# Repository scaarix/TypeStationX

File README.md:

# TypeStationX

AKA PS2-KB

# Update
PCB arrived now waiting for parts to arrive

# About
a single mcu RP2040 based keyboard that uses ps2 controller connectors

currently in development
when ordering pcbs make sure to upload and order both<a href="https://github.com/scaarix/ps2-keyboard-thing/blob/main/TypeStationX/gerbers/left.zip"> left</a> and <a href="https://github.com/scaarix/ps2-keyboard-thing/blob/main/TypeStationX/gerbers/left.zip">right</a> sides
# Findings:
I don't think there are any ps2 controller extension cables that have all 9 pins available. Because one of the pins aren't needed, they get rid of it to save a few cents. So making your own cable is nessisary.
If i make a rev2 (i probably won't) it would most likely have an IO expander on the other half using spi (6 pins on the connector) so that I can use the cable instead of having to create my own.

# TODO:
- [x] Create firmware
- [ ] Create build guide
- [ ] Buy pcb and assemble
- [ ] Add photos

# Parts
| Part name                         | Amount       |Link                                                                                                   |
| --------------------------------- | ------------ | ------------------------------------------------------------------------------------------            |
| KB2040                            | 1            | <a href="https://www.adafruit.com/product/5302">Adafruit</a>|
| 1N4148W Diode                     | 36           |<a href="https://www.adafruit.com/product/5099">AdaFruit</a> |
| 1N4148TR Diode (THT)              | 36           | <a href="https://www.aliexpress.com/item/32729204179.html">Aliexpress</a>|
| Female controller ports           | 2            |<a href="https://www.aliexpress.com/item/1005005547168036.html?spm=a2g0o.productlist.main.47.63aa6e50gPBv1v&algo_pvid=186e3400-9a3a-4116-adb0-feedf2eab064">Aliexpress</a>|
| Male Controller Port              | 2            |<a href="https://www.aliexpress.com/item/1005003234151343.html">Aliexpress</a>|
| Your choice of mx switches        | 36           |                                                                                                       |
| 6mmx3mm magnets                   | 10           |<a href="https://www.amazon.com/FINDMAG-Magnets-Magnetic-Whiteboard-Refrigerator/dp/B08M3YP56J">Amazon</a>|

WARNING: Your PS2 controller cable extension may only have 8 out of the 9 pins needed. You can dissasemble the connector piece and add another pin yourself. Depending on your case it may be better just to use two ps2 controllers to make your own cable!

# HUGE THANKS TO
Chewiedies for helping make the stunning case :)

Corvett for giving me the idea for using the ps2 connector to bridge the two halfs of the keyboard

The absolem server for putting up with my sometimes stupid questions and helping me along the way

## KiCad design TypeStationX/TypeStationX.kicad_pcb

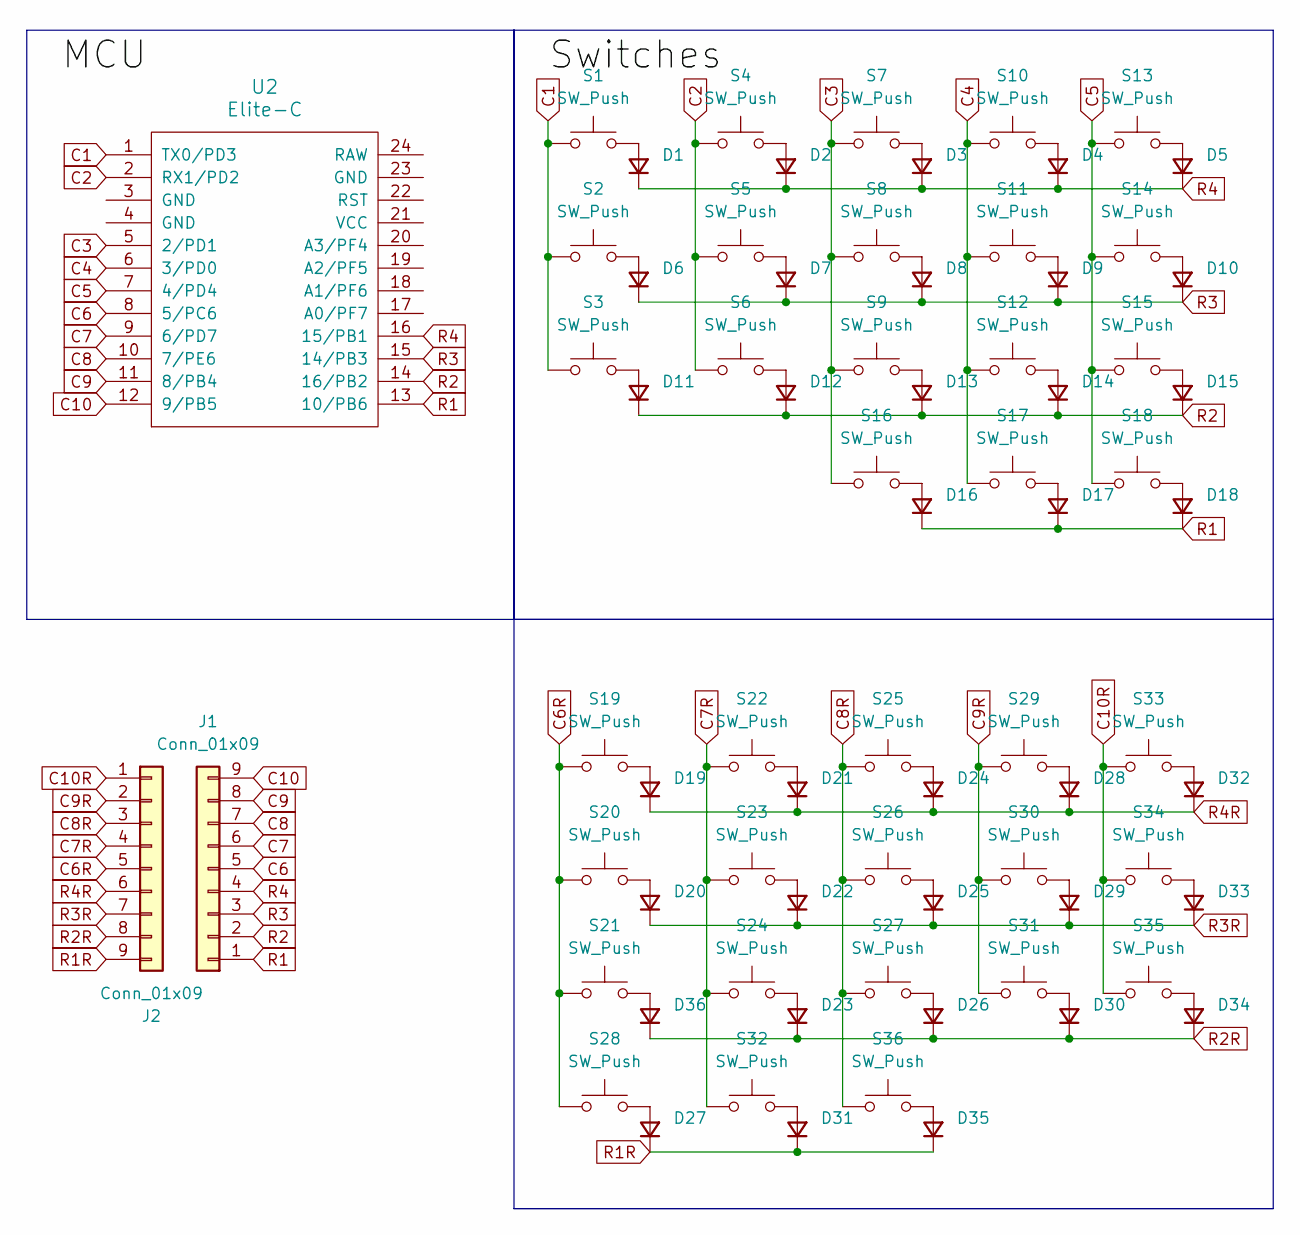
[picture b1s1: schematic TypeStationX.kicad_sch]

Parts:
D1, D2, D3, D4, D5, D6, D7, D8, D9, D10, D11, D12, D13, D14, D15, D16, D17, D18, D19, D20, D21, D22, D23, D24, D25, D26, D27, D28, D29, D30, D31, D32, D33, D34, D35, D36: D_Small; D3_TH_SMD_v2
J1, J2: Conn_01x09; 1x9 4mm
S1, S2, S3, S4, S5, S6, S7, S8, S9, S10, S11, S12, S13, S14, S15, S16, S17, S18, S19, S20, S21, S22, S23, S24, S25, S26, S27, S28, S29, S30, S31, S32, S33, S34, S35, S36: SW_Push; SW_Cherry_MX_PCB_1.00u
U2: Elite-C; ArduinoProMicro

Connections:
C1: S1.1, S2.1, S3.1, U2.1 (TX0/PD3)
C2: S4.1, S5.1, S6.1, U2.2 (RX1/PD2)
C3: S7.1, S8.1, S9.1, S16.1, U2.5 (2/PD1)
C4: S10.1, S11.1, S12.1, S17.1, U2.6 (3/PD0)
C5: S13.1, S14.1, S15.1, S18.1, U2.7 (4/PD4)
C6: J1.5, U2.8 (5/PC6)
C6R: J2.5, S19.1, S20.1, S21.1, S28.1
C7: J1.6, U2.9 (6/PD7)
C7R: J2.4, S22.1, S23.1, S24.1, S32.1
C8: J1.7, U2.10 (7/PE6)
C8R: J2.3, S25.1, S26.1, S27.1, S36.1
C9: J1.8, U2.11 (8/PB4)
C9R: J2.2, S29.1, S30.1, S31.1
C10: J1.9, U2.12 (9/PB5)
C10R: J2.1, S33.1, S34.1, S35.1
unnamed: D1.2 (A), S1.2
unnamed: D2.2 (A), S4.2
unnamed: D3.2 (A), S7.2
unnamed: D4.2 (A), S10.2
unnamed: D5.2 (A), S13.2
unnamed: D6.2 (A), S2.2
unnamed: D7.2 (A), S5.2
unnamed: D8.2 (A), S8.2
unnamed: D9.2 (A), S11.2
unnamed: D10.2 (A), S14.2
unnamed: D11.2 (A), S3.2
unnamed: D12.2 (A), S6.2
unnamed: D13.2 (A), S9.2
unnamed: D14.2 (A), S12.2
unnamed: D15.2 (A), S15.2
unnamed: D16.2 (A), S16.2
unnamed: D17.2 (A), S17.2
unnamed: D18.2 (A), S18.2
unnamed: D19.2 (A), S19.2
unnamed: D20.2 (A), S20.2
unnamed: D21.2 (A), S22.2
unnamed: D22.2 (A), S23.2
unnamed: D23.2 (A), S24.2
unnamed: D24.2 (A), S25.2
unnamed: D25.2 (A), S26.2
unnamed: D26.2 (A), S27.2
unnamed: D27.2 (A), S28.2
unnamed: D28.2 (A), S29.2
unnamed: D29.2 (A), S30.2
unnamed: D30.2 (A), S31.2
unnamed: D31.2 (A), S32.2
unnamed: D32.2 (A), S33.2
unnamed: D33.2 (A), S34.2
unnamed: D34.2 (A), S35.2
unnamed: D35.2 (A), S36.2
unnamed: D36.2 (A), S21.2
R1: D16.1 (K), D17.1 (K), D18.1 (K), J1.1, U2.13 (10/PB6)
R1R: D27.1 (K), D31.1 (K), D35.1 (K), J2.9
R2: D11.1 (K), D12.1 (K), D13.1 (K), D14.1 (K), D15.1 (K), J1.2, U2.14 (16/PB2)
R2R: D23.1 (K), D26.1 (K), D30.1 (K), D34.1 (K), D36.1 (K), J2.8
R3: D6.1 (K), D7.1 (K), D8.1 (K), D9.1 (K), D10.1 (K), J1.3, U2.15 (14/PB3)
R3R: D20.1 (K), D22.1 (K), D25.1 (K), D29.1 (K), D33.1 (K), J2.7
R4: D1.1 (K), D2.1 (K), D3.1 (K), D4.1 (K), D5.1 (K), J1.4, U2.16 (15/PB1)
R4R: D19.1 (K), D21.1 (K), D24.1 (K), D28.1 (K), D32.1 (K), J2.6

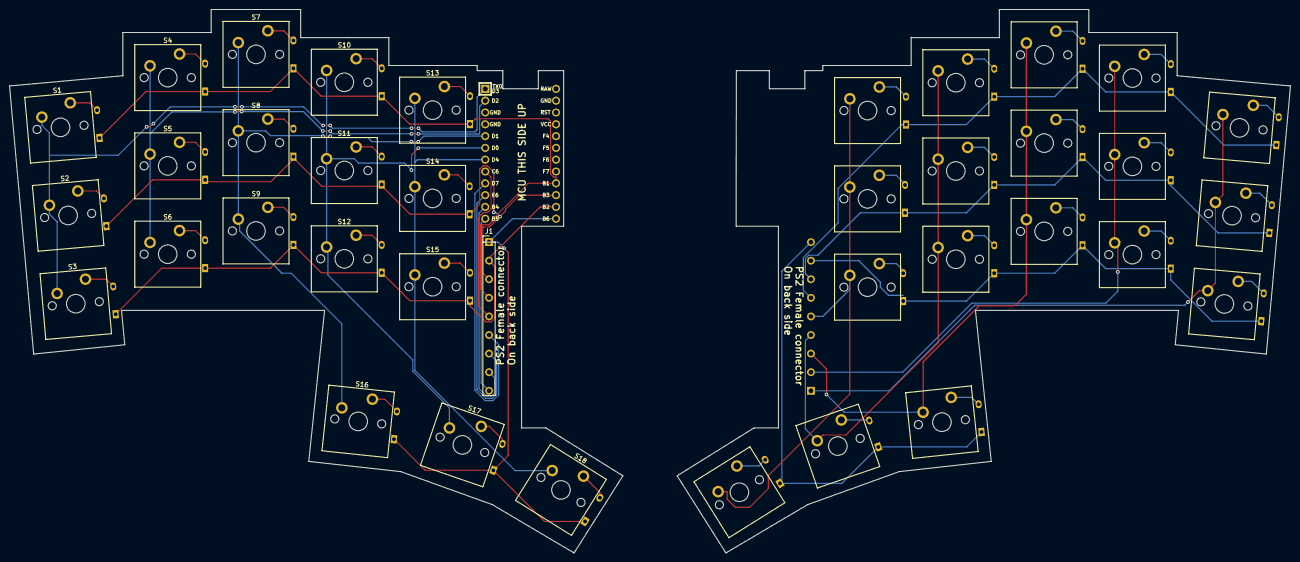
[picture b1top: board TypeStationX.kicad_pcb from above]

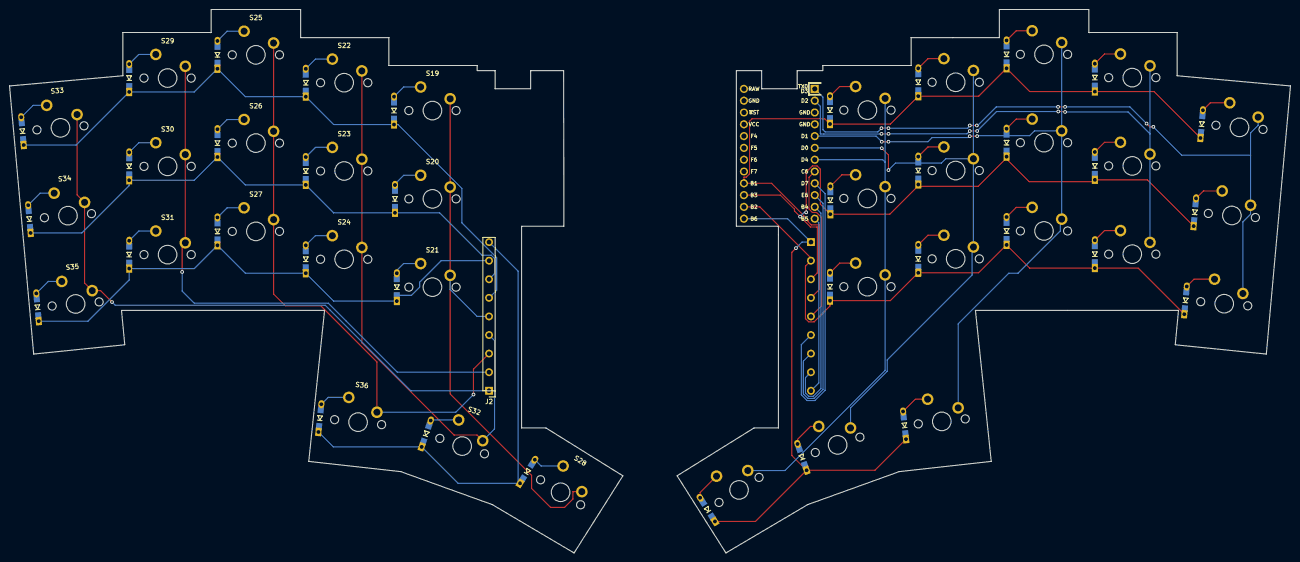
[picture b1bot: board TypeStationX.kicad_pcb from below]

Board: 2 copper layers, 275.7 x 117.0 mm, 75 parts (37 on the bottom side), 59 nets.

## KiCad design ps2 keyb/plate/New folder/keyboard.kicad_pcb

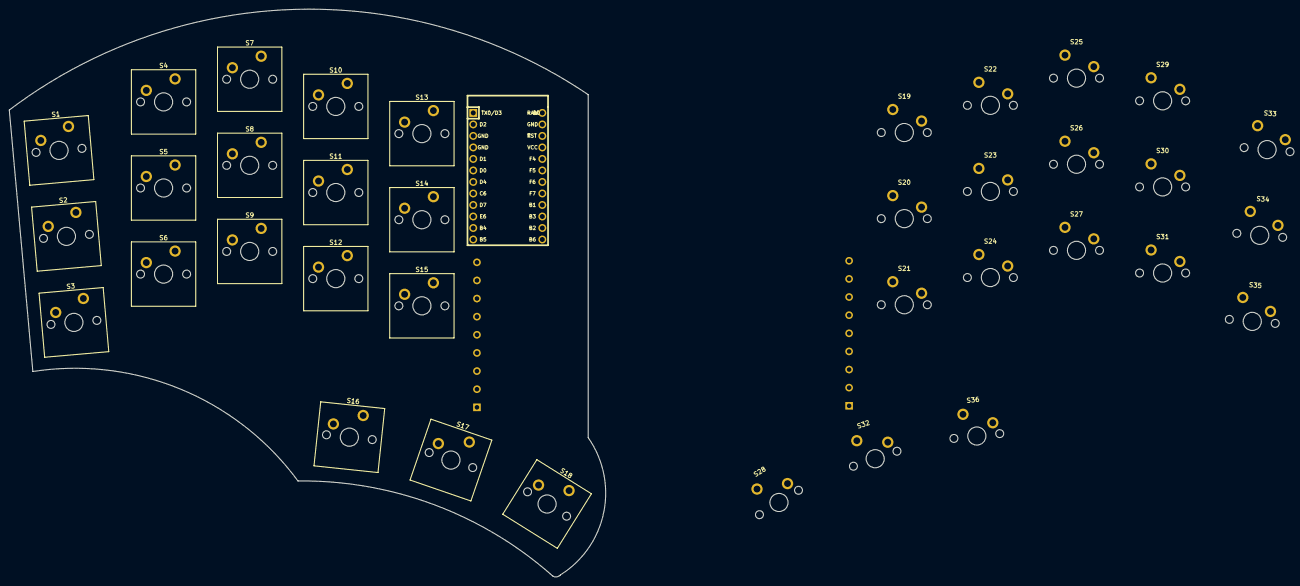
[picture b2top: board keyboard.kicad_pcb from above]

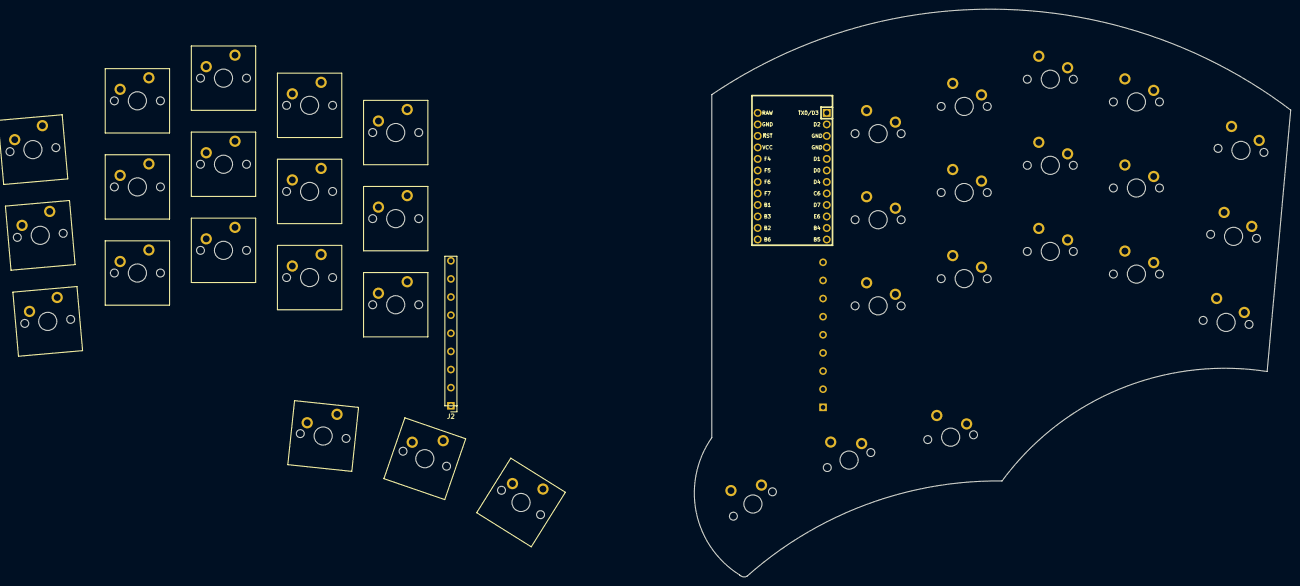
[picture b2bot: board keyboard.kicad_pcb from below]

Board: 2 copper layers, 131.6 x 125.3 mm, 39 parts (20 on the bottom side), 14 nets, no tracks yet.

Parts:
J1: TO_PSX_PAD; PSX_Pad_Connector
J2: Conn_01x09; 1x9 4mm
S1, S2, S3, S4, S5, S6, S7, S8, S9, S10, S11, S12, S13, S14, S15, S16, S17, S18, S19, S20, S21, S22, S23, S24, S25, S26, S27, S28, S29, S30, S31, S32, S33, S34, S35, S36: SW_Push; SW_Cherry_MX_PCB_1.00u
U2: ProMicro; ArduinoProMicro

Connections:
C1: S1.1, S2.1, S3.1, U2.1 (TX0/PD3)
C2: S4.1, S5.1, S6.1, U2.2 (RX1/PD2)
C3: S7.1, S8.1, S9.1, S16.1, U2.5 (2/PD1)
C4: S10.1, S11.1, S12.1, S17.1, U2.6 (3/PD0)
C5: S13.1, S14.1, S15.1, S18.1, U2.7 (4/PD4)
C6: J2.5, S19.1, S20.1, S21.1, S28.1, U2.8 (5/PC6)
C7: J2.4, S22.1, S23.1, S24.1, S32.1, U2.9 (6/PD7)
C8: J2.3, S25.1, S26.1, S27.1, S36.1, U2.10 (7/PE6)
C9: J2.2, S29.1, S30.1, S31.1, U2.11 (8/PB4)
C10: J2.1, S33.1, S34.1, S35.1, U2.12 (9/PB5)
R1: J2.9, U2.13 (10/PB6)
R2: J2.8, U2.14 (16/PB2)
R3: J2.7, U2.15 (14/PB3)
R4: J2.6, U2.16 (15/PB1)

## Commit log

2023-11-24 Updated PCB to have through hole diode support
2023-11-26 Fixed diodes to be on the same side on both halves of the keyboard
